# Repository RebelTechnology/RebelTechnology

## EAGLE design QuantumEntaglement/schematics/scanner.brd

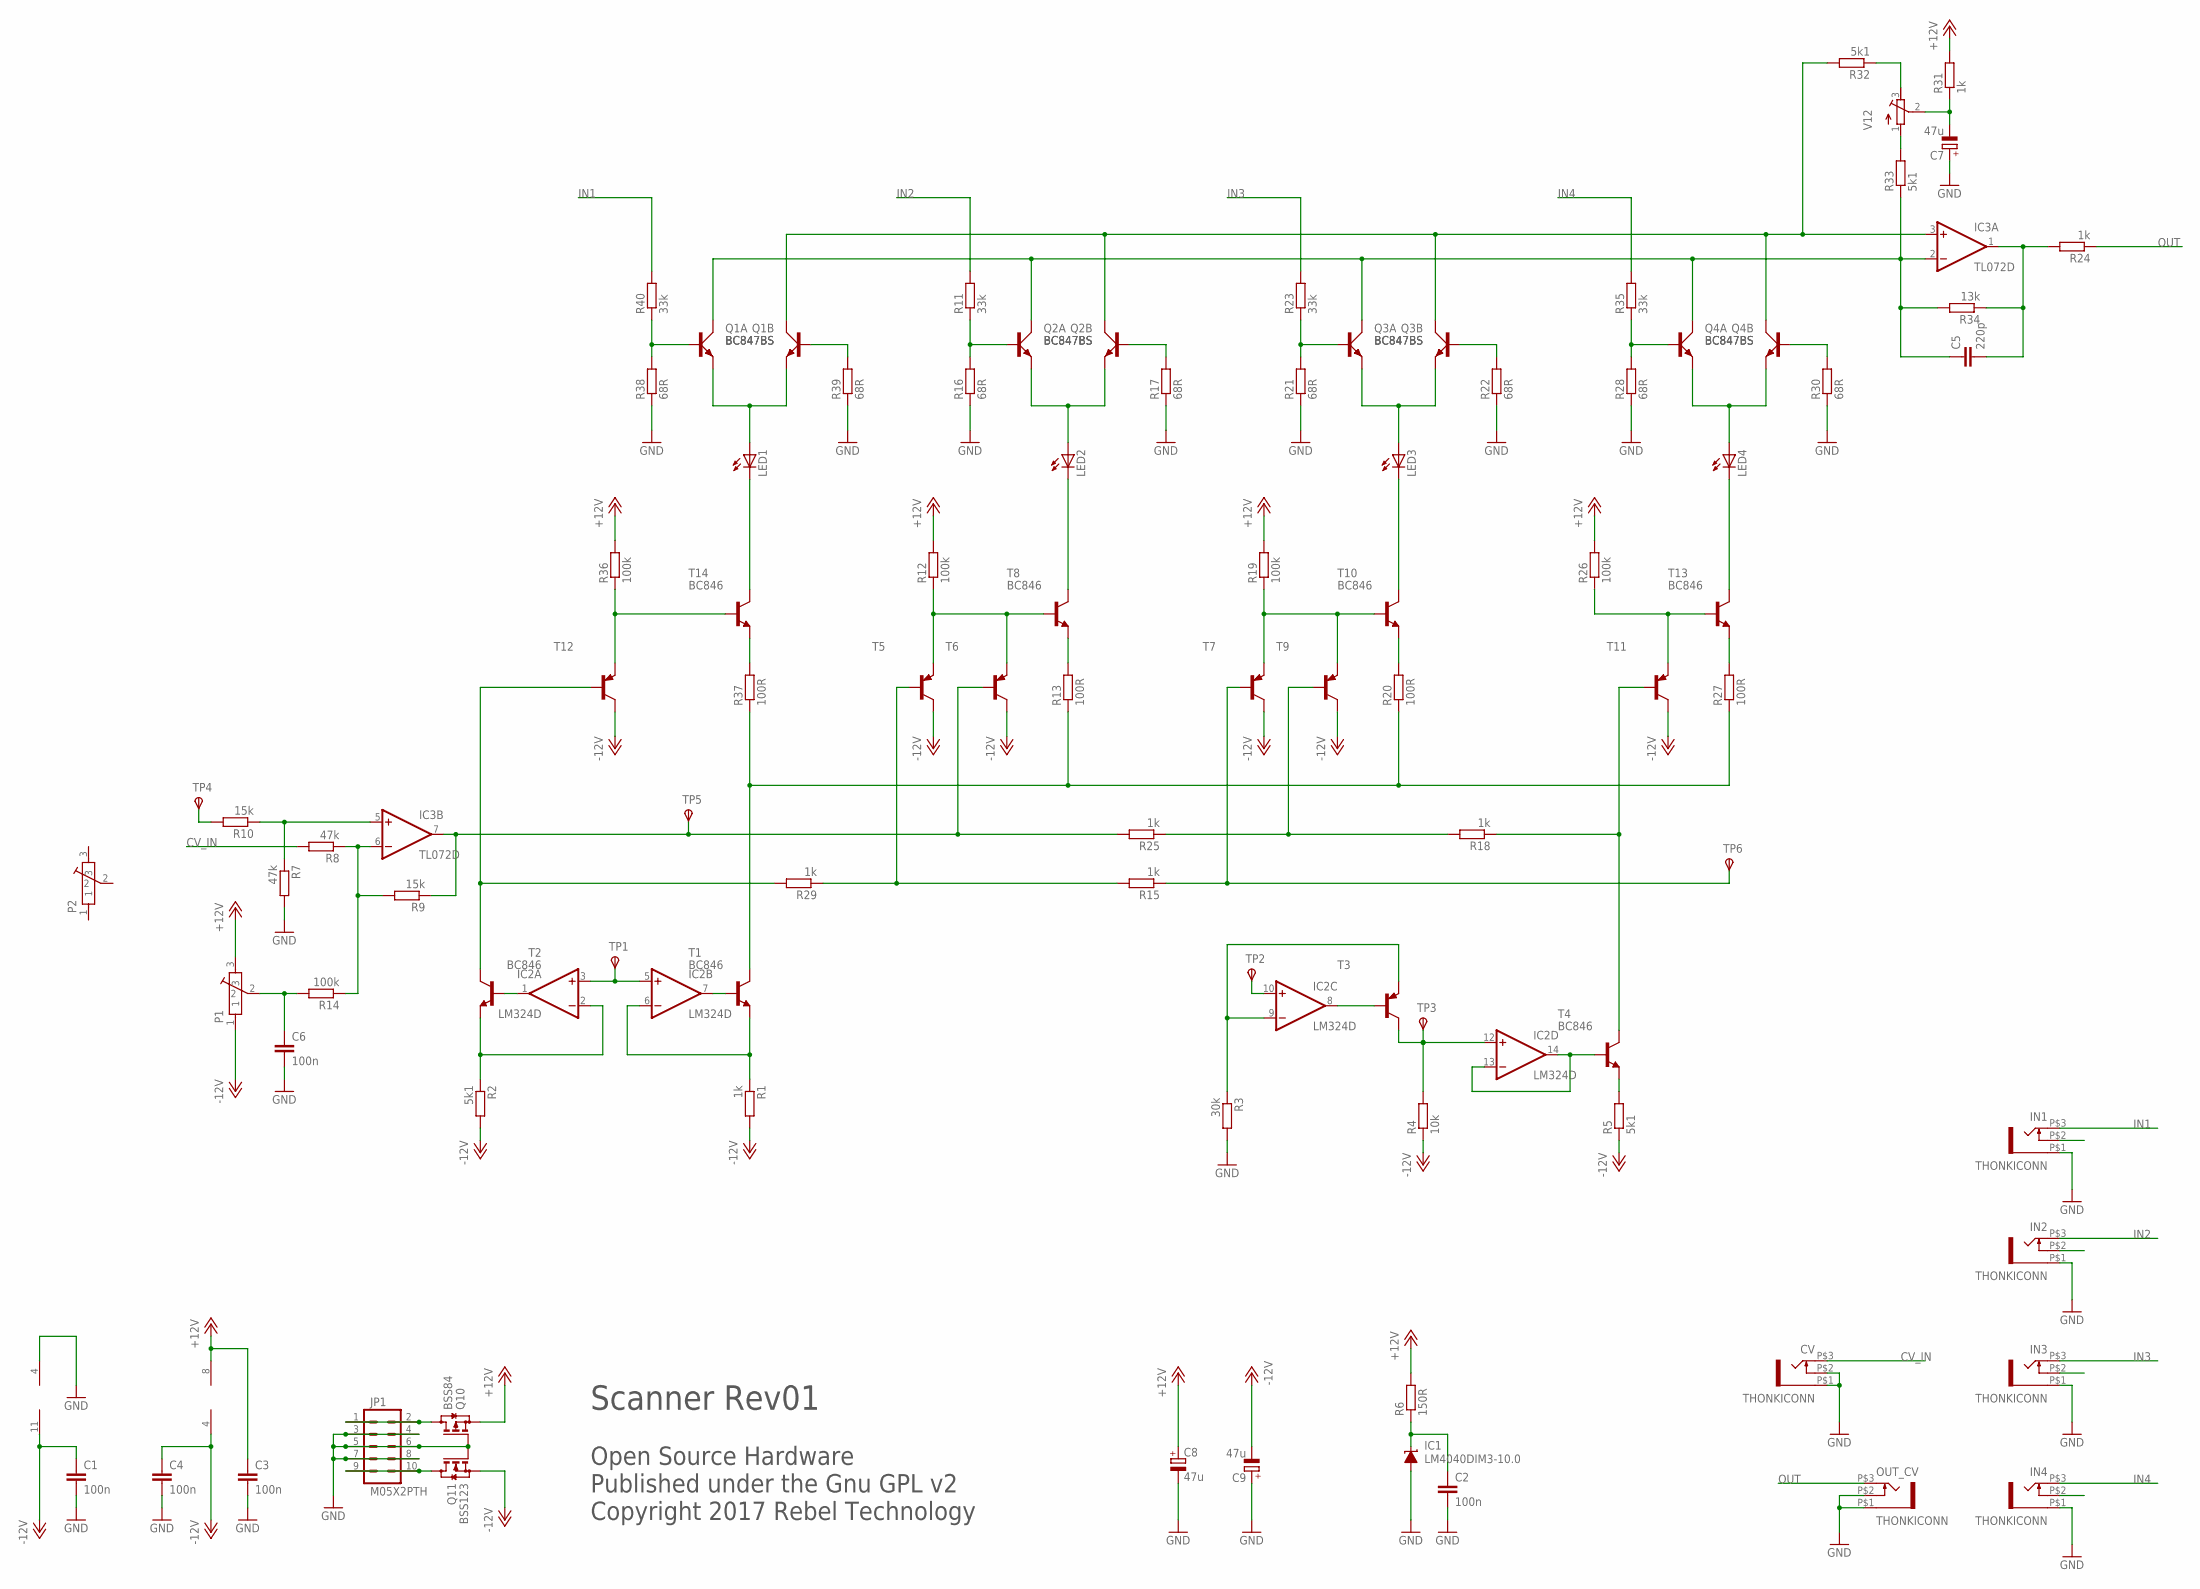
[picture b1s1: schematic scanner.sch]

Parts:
C1, C2, C3, C4, C6: 100n; C0603
C5: 220p; C0603
C7, C8, C9: 47u; CPOL-5
CV: THONKICONN
IC1: LM4040DIM3-10.0; DBZ_R-PDSO-G3
IC2: LM324D; SO14
IC3: TL072D; SO08
IN1, IN2, IN3, IN4: THONKICONN
JP1: M05X2PTH; AVR_ICSP
LED1, LED2, LED3, LED4: LED3MM
OUT_CV: THONKICONN
P1, P2: POT-ALPS-RK09L1140
Q1, Q2, Q3, Q4: BC847BS; SOT363_PHILIPS
Q10: BSS84; SOT23
Q11: BSS123; SOT23
R1, R15, R18, R24, R25, R29, R31: 1k; 0603
R2, R5, R32, R33: 5k1; 0603
R3: 30k; 0603
R4: 10k; 0603
R6: 150R; 0603
R7, R8: 47k; 0603
R9, R10: 15k; 0603
R11, R23, R35, R40: 33k; 0603
R12, R14, R19, R26, R36: 100k; 0603
R13, R20, R27, R37: 100R; 0603
R16, R17, R21, R22, R28, R30, R38, R39: 68R; 0603
R34: 13k; 0603
T1, T2, T4, T8, T10, T13, T14: BC846; SOT23
T3, T5, T6, T7, T9, T11, T12: BC856A-PNP-SOT23-BEC; SOT23-BEC
TP1, TP2, TP3, TP4, TP5, TP6: TPSPAD1-13; P1-13
V12: R-TRIMM64W; RTRIM64W

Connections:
+12V: C3.1, C8.+, IC3.8 (V+), P1.3, Q10.2 (S), R6.2, R12.2, R19.2, R26.2, R31.2, R36.2
-12V: C1.1, C4.1, C9.-, IC2.11 (V-), IC3.4 (V-), P1.1, Q11.2 (S), R1.2, R2.2, R4.1, R5.1, T5.C, T6.C, T7.C, T9.C, T11.C, T12.C
CV_IN: CV.P$3 (3), R8.2
GND: C1.2, C2.2, C3.2, C4.2, C6.2, C7.+, C8.-, C9.+, CV.P$1 (5), CV.P$2 (4), IC1.2 (A), IC2.4 (V+), IN1.P$1 (5), IN2.P$1 (5), IN3.P$1 (5), IN4.P$1 (5), JP1.3, JP1.4, JP1.5, JP1.6, JP1.7, JP1.8, OUT_CV.P$1 (5), OUT_CV.P$2 (4), Q10.1 (G), Q11.1 (G), R3.2, R7.2, R16.1, R17.1, R21.1, R22.1, R28.1, R30.1, R38.1, R39.1
IN1: IN1.P$3 (3), R40.2
IN2: IN2.P$3 (3), R11.2
IN3: IN3.P$3 (3), R23.2
IN4: IN4.P$3 (3), R35.2
unnamed: JP1.9, JP1.10, Q11.3 (D)
unnamed: C6.1, P1.2, R14.2
unnamed: Q3.2 (B), R21.2, R23.1
unnamed: Q3.5 (B), R22.2
unnamed: LED3.A, Q3.1 (E), Q3.4 (E)
unnamed: R19.1, T7.E, T9.E, T10.1 (B)
unnamed: LED3.K (C), T10.3 (C)
unnamed: R20.2, T10.2 (E)
unnamed: R18.1, T4.3 (C), T11.B
unnamed: R15.1, T7.B, TP6.TP
unnamed: C5.1, IC3.2 (-IN), Q1.6 (C), Q2.6 (C), Q3.6 (C), Q4.6 (C), R33.1, R34.2
unnamed: R18.2, R25.1, T9.B
unnamed: R13.1, R20.1, R27.1, R37.1, T1.3 (C)
unnamed: IC2.13 (-IN), IC2.14 (OUT), T4.1 (B)
unnamed: IC2.8 (OUT), T3.B
unnamed: IC2.12 (+IN), R4.2, T3.C, TP3.TP
unnamed: R5.2, T4.2 (E)
unnamed: IC2.9 (-IN), R3.1, T3.E
unnamed: IC2.10 (+IN), TP2.TP
unnamed: IC2.1 (OUT), T2.1 (B)
unnamed: IC2.7 (OUT), T1.1 (B)
unnamed: IC2.3 (+IN), IC2.5 (+IN), TP1.TP
unnamed: IC2.6 (-IN), R1.1, T1.2 (E)
unnamed: IC2.2 (-IN), R2.1, T2.2 (E)
unnamed: IC3.6 (-IN), R8.1, R9.2, R14.1
unnamed: R10.2, TP4.TP
unnamed: IC3.5 (+IN), R7.1, R10.1
unnamed: JP1.1, JP1.2, Q10.3 (D)
unnamed: C2.1, IC1.1 (C), R6.1
unnamed: C5.2, IC3.1 (OUT), R24.2, R34.1
unnamed: R33.2, V12.1 (A)
unnamed: R32.1, V12.3 (E)
unnamed: C7.-, R31.1, V12.2 (S)
unnamed: Q4.2 (B), R28.2, R35.1
unnamed: Q4.5 (B), R30.2
unnamed: LED4.A, Q4.1 (E), Q4.4 (E)
unnamed: R26.1, T11.E, T13.1 (B)
unnamed: LED4.K (C), T13.3 (C)
unnamed: R27.2, T13.2 (E)
unnamed: R29.2, T2.3 (C), T12.B
unnamed: IC3.7 (OUT), R9.1, R25.2, T6.B, TP5.TP
unnamed: Q2.2 (B), R11.1, R16.2
unnamed: Q2.5 (B), R17.2
unnamed: LED2.A, Q2.1 (E), Q2.4 (E)
unnamed: R12.1, T5.E, T6.E, T8.1 (B)
unnamed: LED2.K (C), T8.3 (C)
unnamed: R13.2, T8.2 (E)
unnamed: IC3.3 (+IN), Q1.3 (C), Q2.3 (C), Q3.3 (C), Q4.3 (C), R32.2
unnamed: Q1.2 (B), R38.2, R40.1
unnamed: Q1.5 (B), R39.2
unnamed: LED1.A, Q1.1 (E), Q1.4 (E)
unnamed: R36.1, T12.E, T14.1 (B)
unnamed: LED1.K (C), T14.3 (C)
unnamed: R37.2, T14.2 (E)
unnamed: R15.2, R29.1, T5.B
OUT: OUT_CV.P$3 (3), R24.1

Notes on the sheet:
Open Source Hardware Published under the Gnu GPL v2 Copyright 2017 Rebel Technology
Scanner Rev01

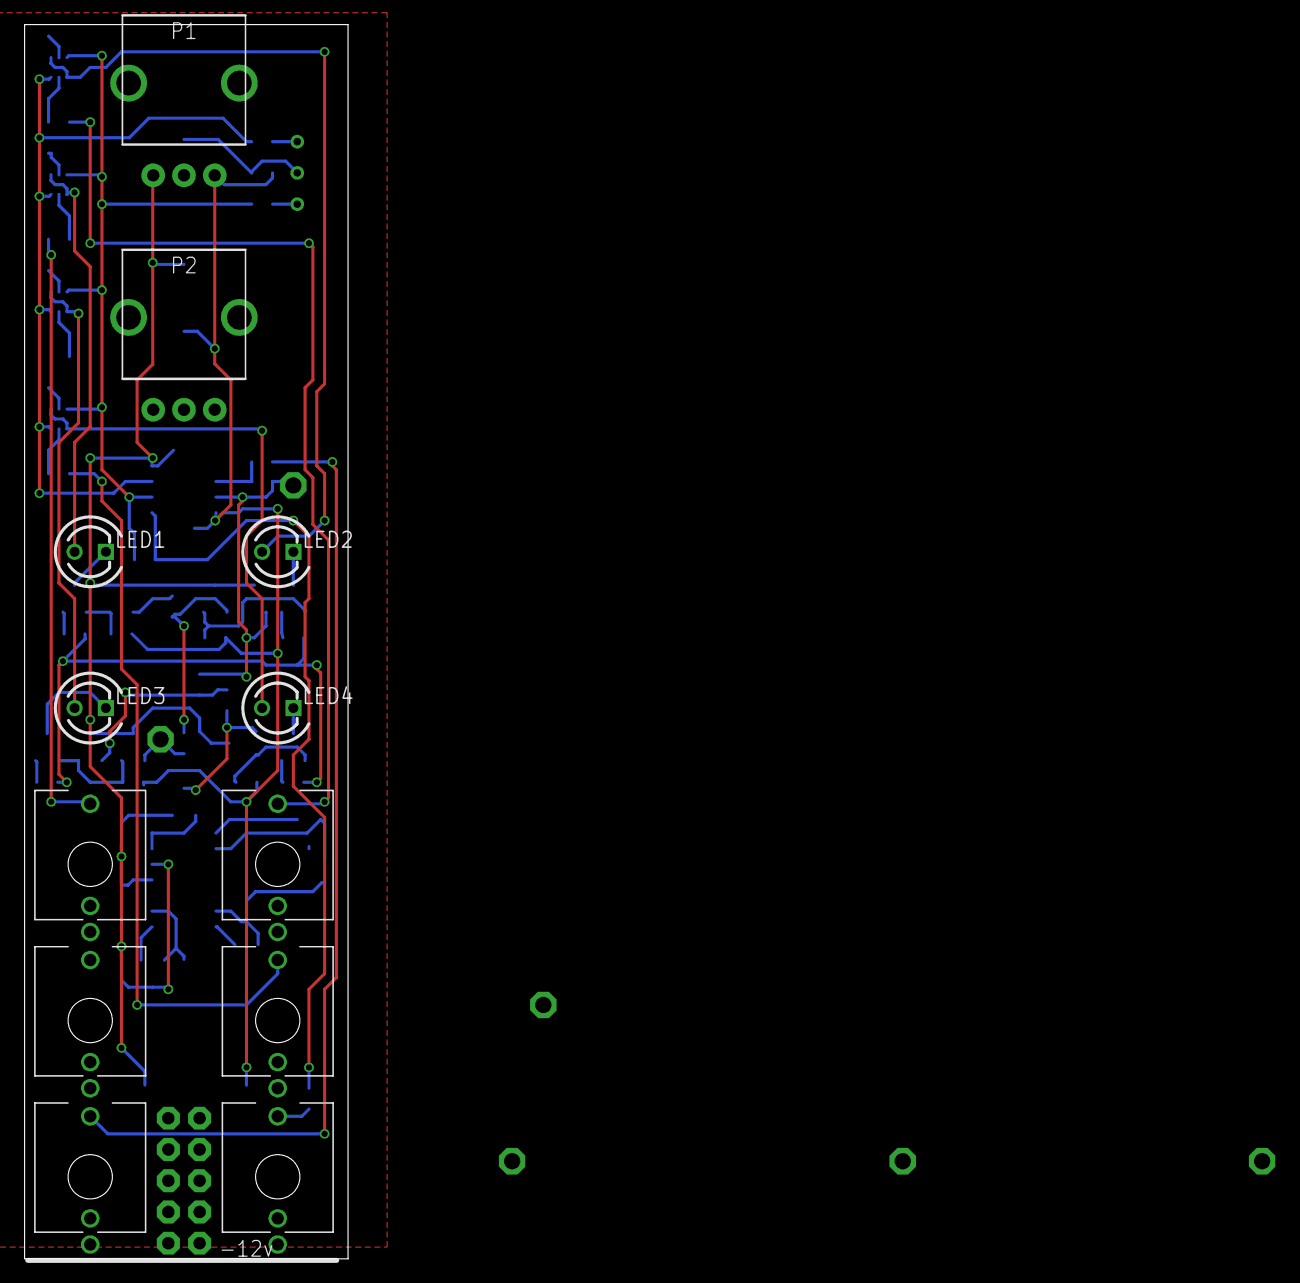
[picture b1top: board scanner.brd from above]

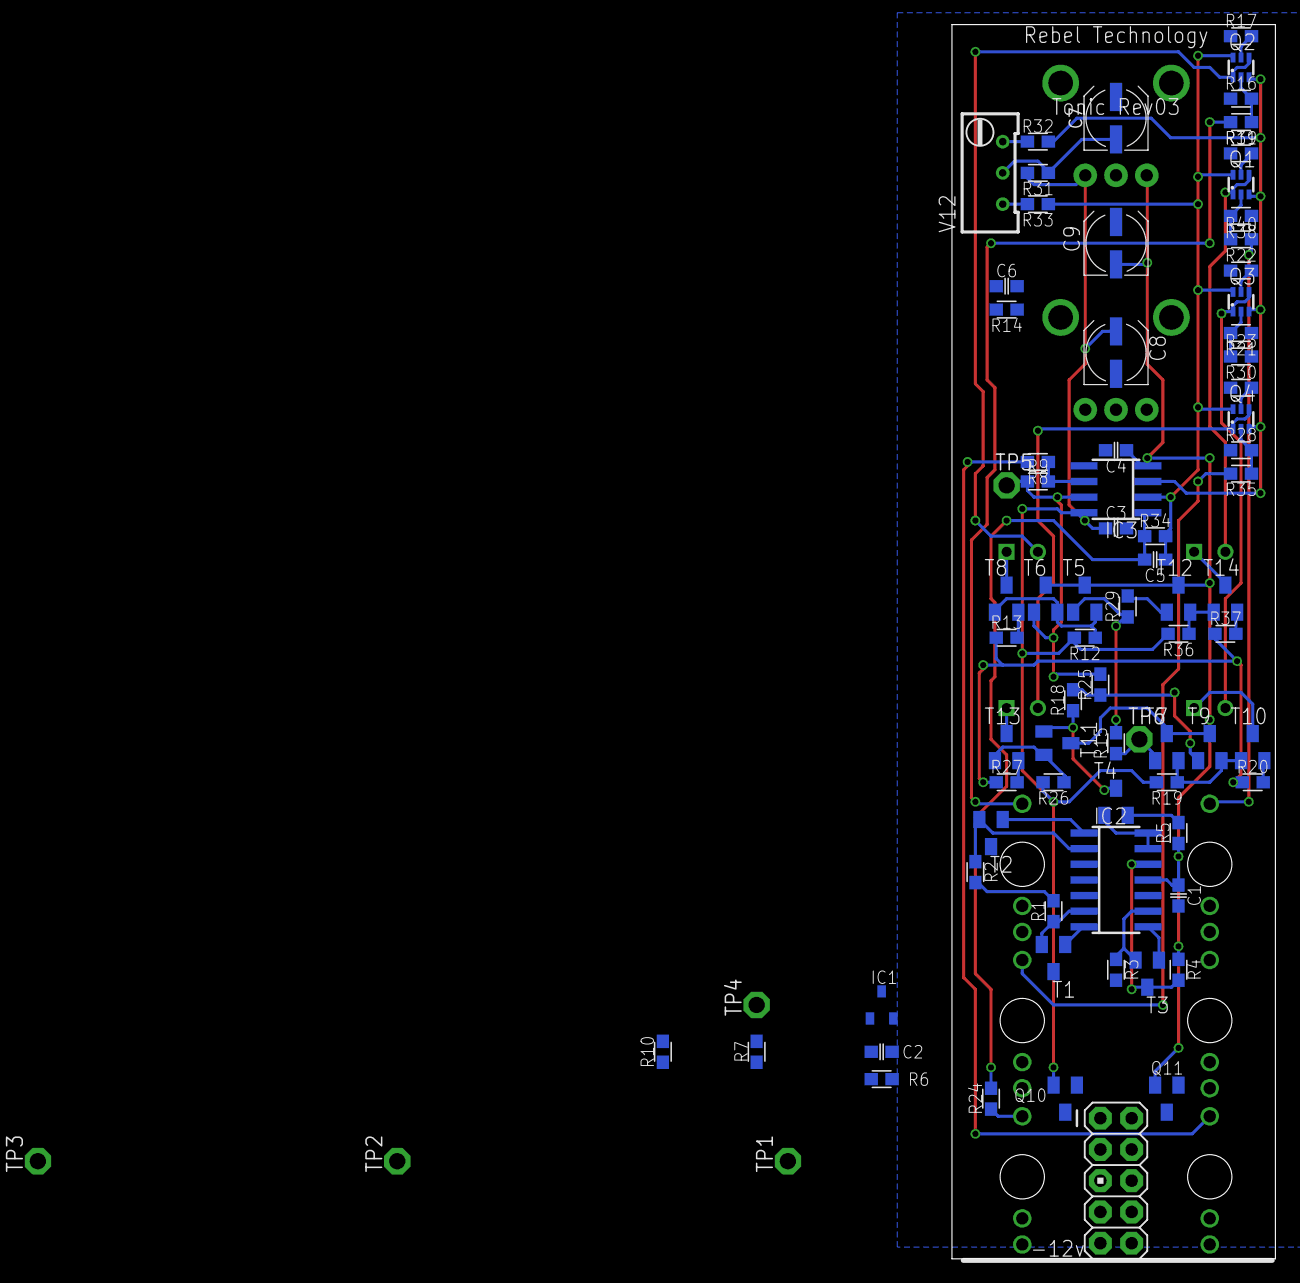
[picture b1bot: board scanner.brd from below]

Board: 2 copper layers, 26.3 x 100.3 mm, 92 parts (80 on the bottom side), 64 nets.

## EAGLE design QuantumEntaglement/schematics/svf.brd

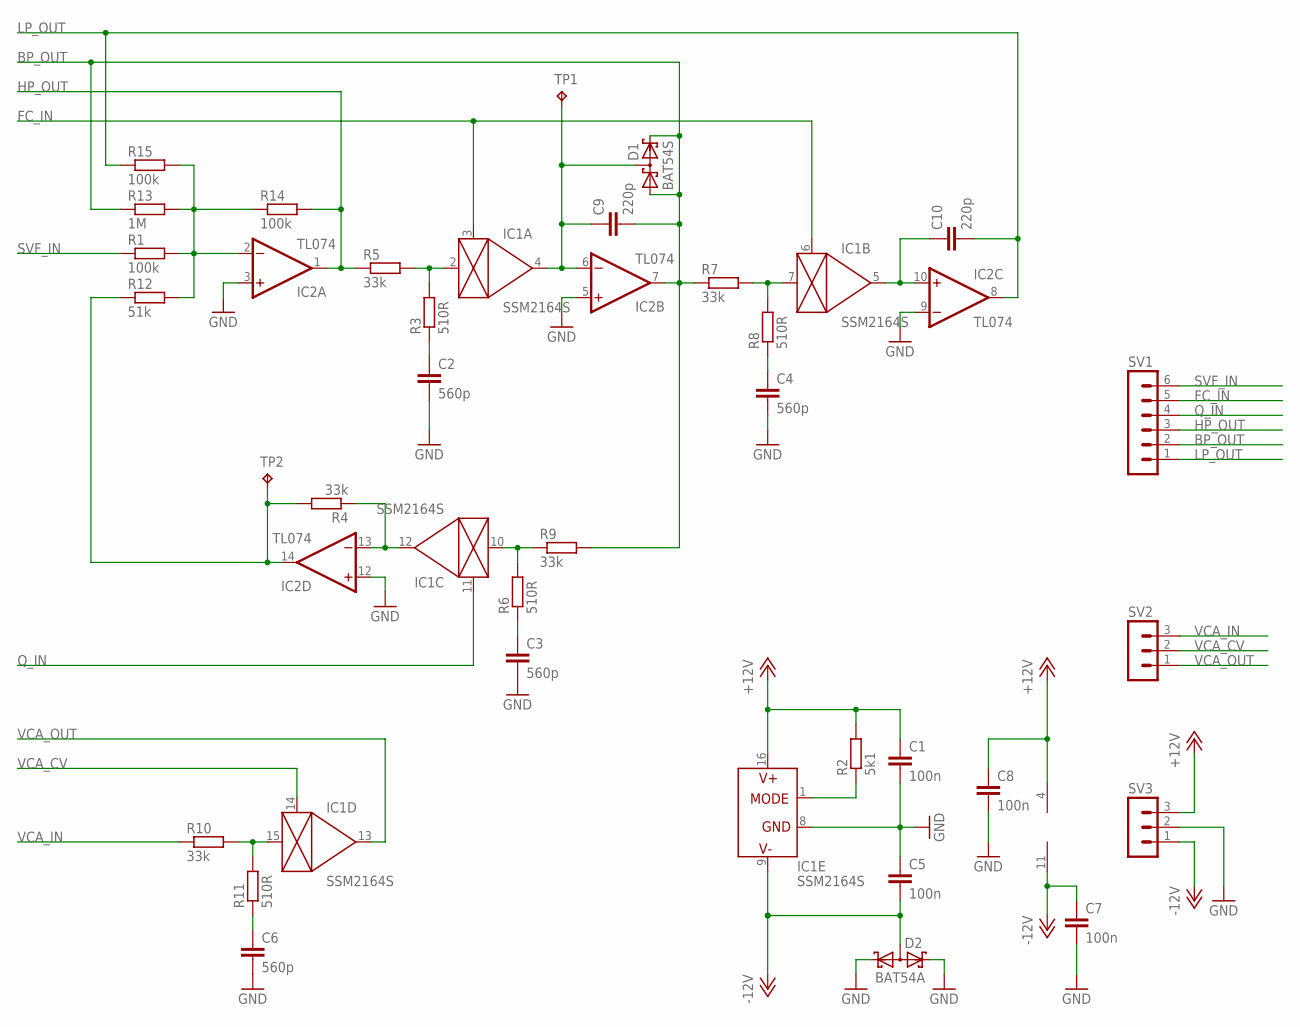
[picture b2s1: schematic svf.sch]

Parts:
C1, C5, C7, C8: 100n; C0603
C2, C3, C4, C6: 560p; C0603
C9, C10: 220p; C0603
D1: BAT54S; SOT23
D2: BAT54A; SOT23
IC1: SSM2164S; SOIC16N
IC2: TL074; SO14
R1, R14, R15: 100k; 0603
R2: 5k1; 0603
R3, R6, R8, R11: 510R; 0603
R4, R5, R7, R9, R10: 33k; 0603
R12: 51k; 0603
R13: 1M; 0603
SV1: MA06-1
SV2, SV3: MA03-1
TP1, TP2: TPPAD1-13; P1-13

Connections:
+12V: C1.1, C8.1, IC1.16 (V+), IC2.4 (V+), R2.2, SV3.3
-12V: C5.2, C7.1, D2.3 (AA), IC1.9 (V-), IC2.11 (V-), SV3.1
BP_OUT: C9.2, D1.1 (A1), D1.2 (C2), IC2.7 (OUT), R7.1, R9.2, R13.1, SV1.2
FB_IN: IC2.14 (OUT), R4.2, R12.1, TP2.TP
FC_IN: IC1.3 (CTRL), IC1.6 (CTRL), SV1.5
GND: C1.2, C2.2, C3.2, C4.2, C5.1, C6.2, C7.2, C8.2, D2.1 (K1), D2.2 (K2), IC1.8 (GND), IC2.3 (+IN), IC2.5 (+IN), IC2.9 (-IN), IC2.12 (+IN), SV3.2
HP_OUT: IC2.1 (OUT), R5.1, R14.2, SV1.3
LP_OUT: C10.2, IC2.8 (OUT), R15.1, SV1.1
unnamed: IC1.1 (MODE), R2.1
unnamed: IC1.7 (IN), R7.2, R8.2
unnamed: C4.1, R8.1
unnamed: C10.1, IC1.5 (OUT), IC2.10 (+IN)
unnamed: IC1.12 (OUT), IC2.13 (-IN), R4.1
unnamed: IC2.2 (-IN), R1.2, R12.2, R13.2, R14.1, R15.2
unnamed: C6.1, R11.1
unnamed: C9.1, D1.3 (C1A2), IC1.4 (OUT), IC2.6 (-IN), TP1.TP
unnamed: IC1.10 (IN), R6.2, R9.1
unnamed: IC1.15 (IN), R10.2, R11.2
unnamed: C3.1, R6.1
unnamed: IC1.2 (IN), R3.2, R5.2
unnamed: C2.1, R3.1
Q_IN: IC1.11 (CTRL), SV1.4
SVF_IN: R1.1, SV1.6
VCA_CV: IC1.14 (CTRL), SV2.2
VCA_IN: R10.1, SV2.3
VCA_OUT: IC1.13 (OUT), SV2.1

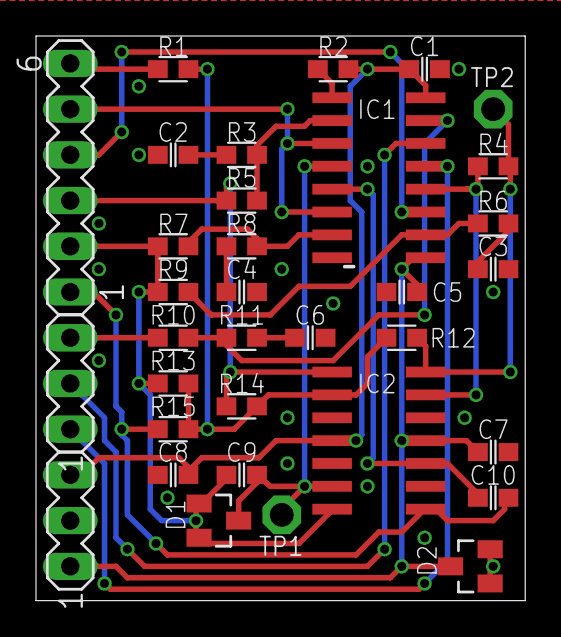
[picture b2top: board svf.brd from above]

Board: 2 copper layers, 27.2 x 31.4 mm, 34 parts (0 on the bottom side), 26 nets.

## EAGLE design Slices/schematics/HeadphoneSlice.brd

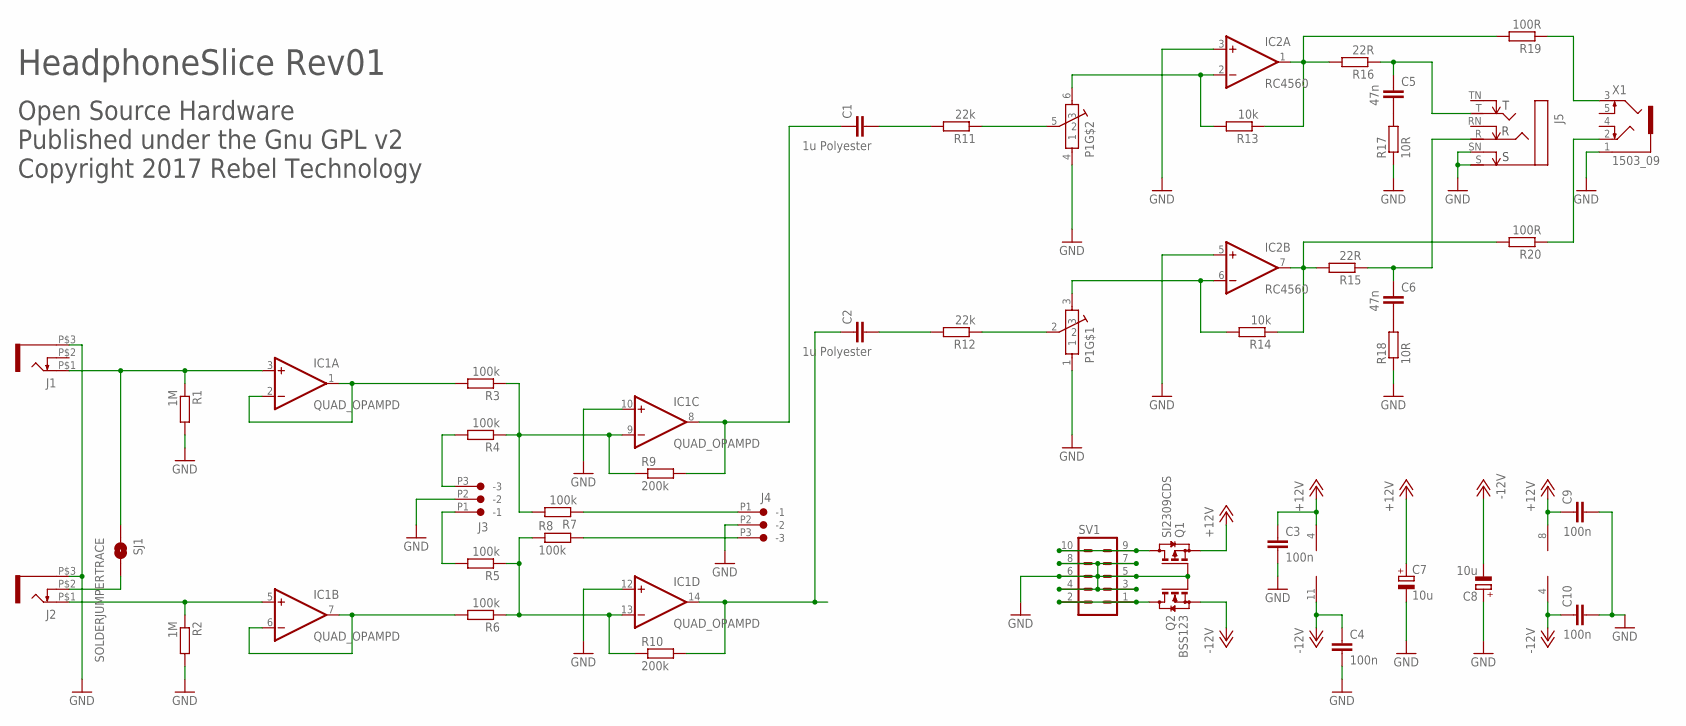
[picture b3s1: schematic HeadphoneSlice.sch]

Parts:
C1, C2: 1u Polyester; C1210
C3, C4, C9, C10: 100n; C0603
C5, C6: 47n; C0603
C7, C8: 10u; 153CLV-0505
IC1: QUAD_OPAMPD; SO14
IC2: RC4560; SO08
J1, J2: JACK-UJ-3502-RSLOT; UJ-3502-R-SLOT
J3, J4: CON-JST_PH_3W
J5: NEUTRIK_NRJ6HFSTD; NRJ6HF
P1: POT-BOURNS-PTD902
Q1: SI2309CDS; SOT23
Q2: BSS123; SOT23
R1, R2: 1M; 0603
R3, R4, R5, R6, R7, R8: 100k; 0603
R9, R10: 200k; 0603
R11, R12: 22k; 0603
R13, R14: 10k; 0603
R15, R16: 22R; 0603
R17, R18: 10R; 0603
R19, R20: 100R; 0603
SJ1: SOLDERJUMPERTRACE; SJ_2S-TRACE
SV1: MA05-2
X1: 1503_09

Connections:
+12V: C3.1, C7.+, C9.1, IC1.4 (V+), IC2.8 (V+), Q1.2 (S)
-12V: C4.1, C8.-, C10.1, IC1.11 (V-), IC2.4 (V-), Q2.2 (S)
BUS_IN_L: J3.P3 (-3), R4.2
BUS_IN_R: J3.P1 (-1), R5.2
GND: C3.2, C4.2, C7.-, C8.+, C9.2, C10.2, IC1.10 (+IN), IC1.12 (+IN), IC2.3 (+IN), IC2.5 (+IN), J1.P$3 (SLEEVE), J2.P$3 (SLEEVE), J3.P2 (-2), J4.P2 (-2), J5.S, J5.SN, P1.1, P1.4 (1), Q1.1 (G), Q2.1 (G), R1.2, R2.2, R17.1, R18.1, SV1.3, SV1.4, SV1.5, SV1.6, SV1.7, SV1.8, X1.1
HP_L: C5.1, J5.T, R16.1
HP_R: C6.1, J5.R, R15.1
IN_B1: J2.P$2 (SW), SJ1.2
IN_L: IC1.3 (+IN), J1.P$1 (TIP), R1.1, SJ1.1
IN_R: IC1.5 (+IN), J2.P$1 (TIP), R2.1
LINE_L: R19.1, X1.3
LINE_R: R20.1, X1.2
unnamed: Q2.3 (D), SV1.1, SV1.2
unnamed: IC2.7 (OUT), R14.1, R15.2, R20.2
unnamed: IC2.2 (-IN), P1.6 (3), R13.2
unnamed: C2.2, R12.2
unnamed: P1.5 (2), R11.1
unnamed: P1.2, R12.1
unnamed: C2.1, IC1.14 (OUT), R10.2
unnamed: C1.2, R11.2
unnamed: C1.1, IC1.8 (OUT), R9.2
unnamed: IC1.6 (-IN), IC1.7 (OUT), R6.2
unnamed: C6.2, R18.2
unnamed: IC1.1 (OUT), IC1.2 (-IN), R3.2
unnamed: Q1.3 (D), SV1.9, SV1.10
unnamed: IC2.6 (-IN), P1.3, R14.2
unnamed: IC2.1 (OUT), R13.1, R16.2, R19.2
unnamed: J4.P1 (-1), R7.1
unnamed: C5.2, R17.2
unnamed: J4.P3 (-3), R8.2
unnamed: IC1.13 (-IN), R5.1, R6.1, R8.1, R10.1
unnamed: IC1.9 (-IN), R3.1, R4.1, R7.2, R9.1

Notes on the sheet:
Open Source Hardware Published under the Gnu GPL v2 Copyright 2017 Rebel Technology
HeadphoneSlice Rev01

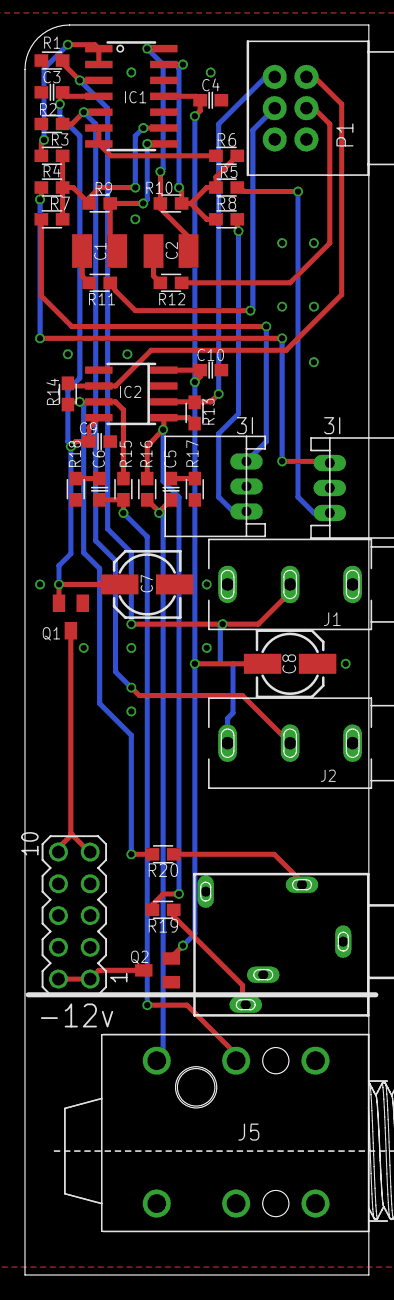
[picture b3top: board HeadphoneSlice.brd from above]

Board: 2 copper layers, 27.5 x 100.0 mm, 43 parts (1 on the bottom side), 32 nets.

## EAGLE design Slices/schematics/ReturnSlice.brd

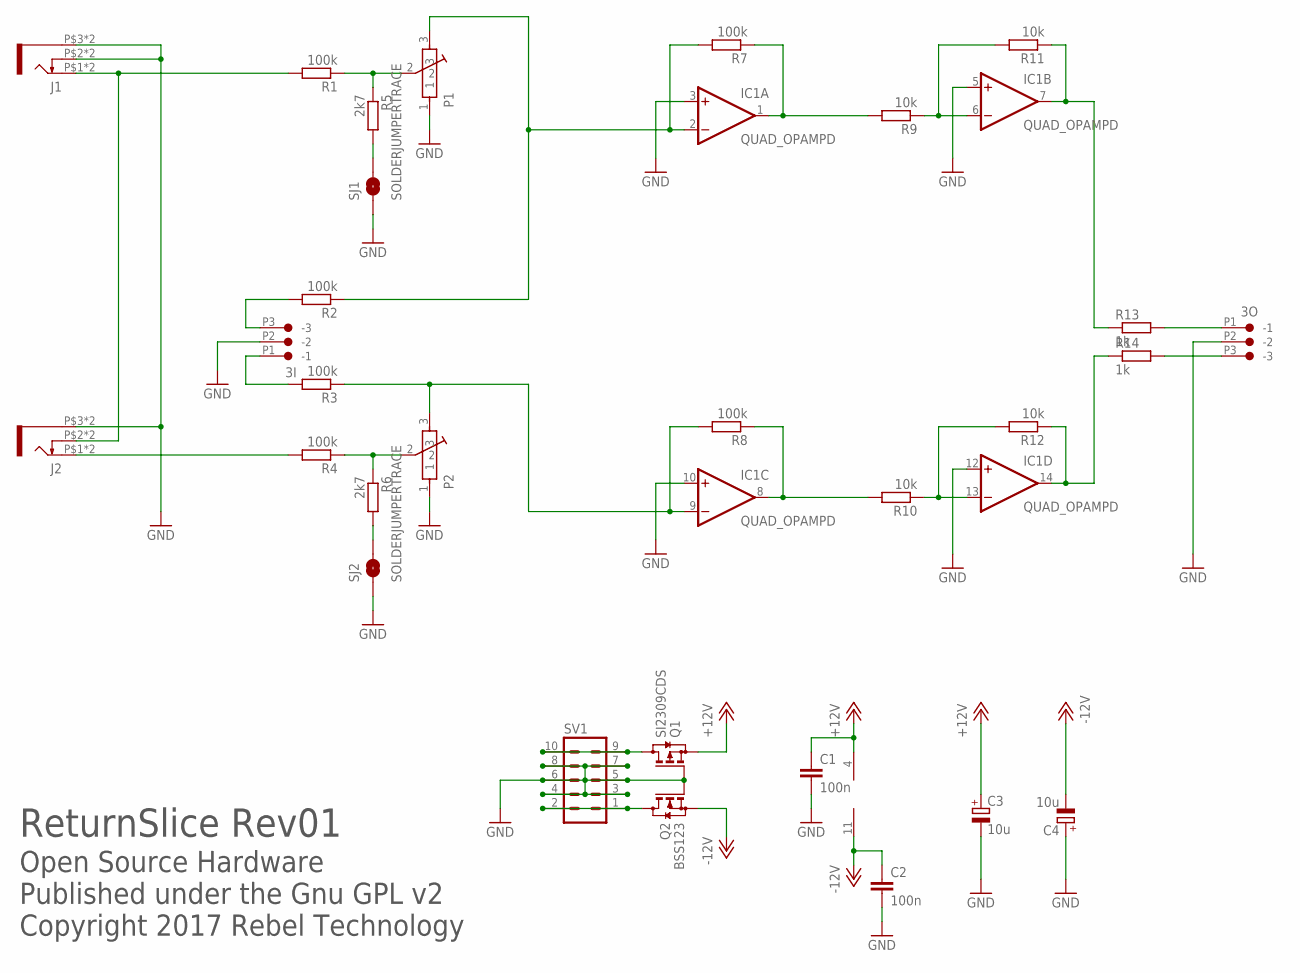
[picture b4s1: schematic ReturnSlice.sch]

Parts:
3I, 3O: CON-JST_PH_3W
C1, C2: 100n; C0603
C3, C4: 10u; 153CLV-0505
IC1: QUAD_OPAMPD; SO14
J1, J2: JACK-UJ-3502-RSLOT; UJ-3502-R-SLOT
P1, P2: 10k; POT-BOURNS-PTD901
Q1: SI2309CDS; SOT23
Q2: BSS123; SOT23
R1, R2, R3, R4, R7, R8: 100k; 0603
R5, R6: 2k7; 0603
R9, R10, R11, R12: 10k; 0603
R13, R14: 1k; 0603
SJ1, SJ2: SOLDERJUMPERTRACE; SJ_2S-TRACE
SV1: MA05-2

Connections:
+12V: C1.1, C3.+, IC1.4 (V+), Q1.2 (S)
-12V: C2.1, C4.-, IC1.11 (V-), Q2.2 (S)
GND: 3I.P2 (-2), 3O.P2 (-2), C1.2, C2.2, C3.-, C4.+, IC1.3 (+IN), IC1.5 (+IN), IC1.10 (+IN), IC1.12 (+IN), J1.P$2 (SW), J1.P$2B (SW), J1.P$3 (SLEEVE), J1.P$3B (SLEEVE), J2.P$3 (SLEEVE), J2.P$3B (SLEEVE), P1.1, P2.1, Q1.1 (G), Q2.1 (G), SJ1.1, SJ2.1, SV1.3, SV1.4, SV1.5, SV1.6, SV1.7, SV1.8
IN_A: 3I.P3 (-3), R2.2
IN_L: J1.P$1 (TIP), J1.P$1B (TIP), J2.P$2 (SW), J2.P$2B (SW), R1.2
IN_R: J2.P$1 (TIP), J2.P$1B (TIP), R4.2
unnamed: Q2.3 (D), SV1.1, SV1.2
unnamed: R5.2, SJ1.2
unnamed: R6.2, SJ2.2
unnamed: IC1.9 (-IN), P2.3, R3.1, R8.2
unnamed: IC1.6 (-IN), R9.1, R11.2
unnamed: 3O.P1 (-1), R13.2
unnamed: 3O.P3 (-3), R14.2
unnamed: IC1.7 (OUT), R11.1, R13.1
unnamed: P2.2, R4.1, R6.1
unnamed: P1.2, R1.1, R5.1
unnamed: Q1.3 (D), SV1.9, SV1.10
unnamed: 3I.P1 (-1), R3.2
unnamed: IC1.2 (-IN), P1.3, R2.1, R7.2
unnamed: IC1.13 (-IN), R10.1, R12.2
unnamed: IC1.14 (OUT), R12.1, R14.1
unnamed: IC1.8 (OUT), R8.1, R10.2
unnamed: IC1.1 (OUT), R7.1, R9.2

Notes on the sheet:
Open Source Hardware Published under the Gnu GPL v2 Copyright 2017 Rebel Technology
ReturnSlice Rev01

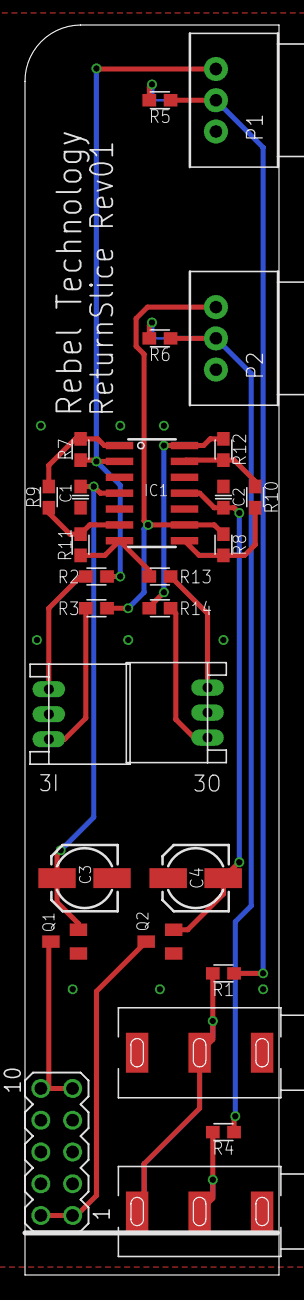
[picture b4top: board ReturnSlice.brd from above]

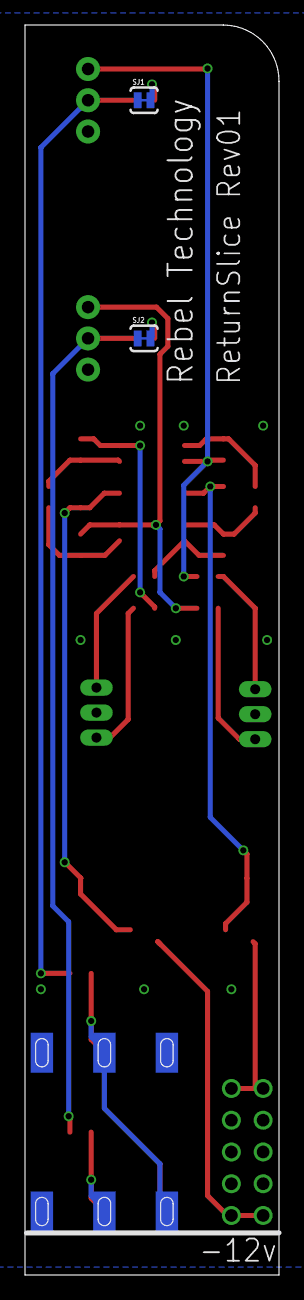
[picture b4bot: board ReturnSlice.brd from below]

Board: 2 copper layers, 20.3 x 100.0 mm, 30 parts (2 on the bottom side), 23 nets.

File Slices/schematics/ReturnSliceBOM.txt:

Partlist exported from C:/cygwin64/home/padski/RebelTechnology/Slices/schematics/ReturnSlice.sch at 17/01/2017 15:00

Qty Value              Device             Package           Parts                  Description                          
1                      MA05-2             MA05-2            SV1                    PIN HEADER                           
6   100k               R-EU_0603          0603              R1, R2, R3, R4, R7, R8 RESISTOR, European symbol            
2   100n               C-EUC0603          C0603             C1, C2                 CAPACITOR, European symbol           
2   10k                POT-BOURNS-PTD901  POT-BOURNS-PTD901 P1, P2                                                      
4   10k                R-EU_0603          0603              R9, R10, R11, R12      RESISTOR, European symbol            
2   10u                CPOL-EU153CLV-0505 153CLV-0505       C3, C4                 POLARIZED CAPACITOR, European symbol 
2   1k                 R-EU_0603          0603              R13, R14               RESISTOR, European symbol            
2   2k7                R-EU_0603          0603              R5, R6                 RESISTOR, European symbol            
1   BSS123             BSS123             SOT23             Q2                     N-CHANNEL MOS FET                    
2   CON-JST_PH_3W      CON-JST_PH_3W      CON-JST_PH_3W     3I, 3O                                                      
2   JACK-UJ-3502-RSLOT JACK-UJ-3502-RSLOT UJ-3502-R-SLOT    J1, J2                                                      
1   QUAD_OPAMPD        QUAD_OPAMPD        SO14              IC1                    OP AMP                               
1   SI2309CDS          BSS84              SOT23             Q1                     P-CHANNEL MOS FET                    
2   SOLDERJUMPERTRACE  SOLDERJUMPERTRACE  SJ_2S-TRACE       SJ1, SJ2               Solder Jumper

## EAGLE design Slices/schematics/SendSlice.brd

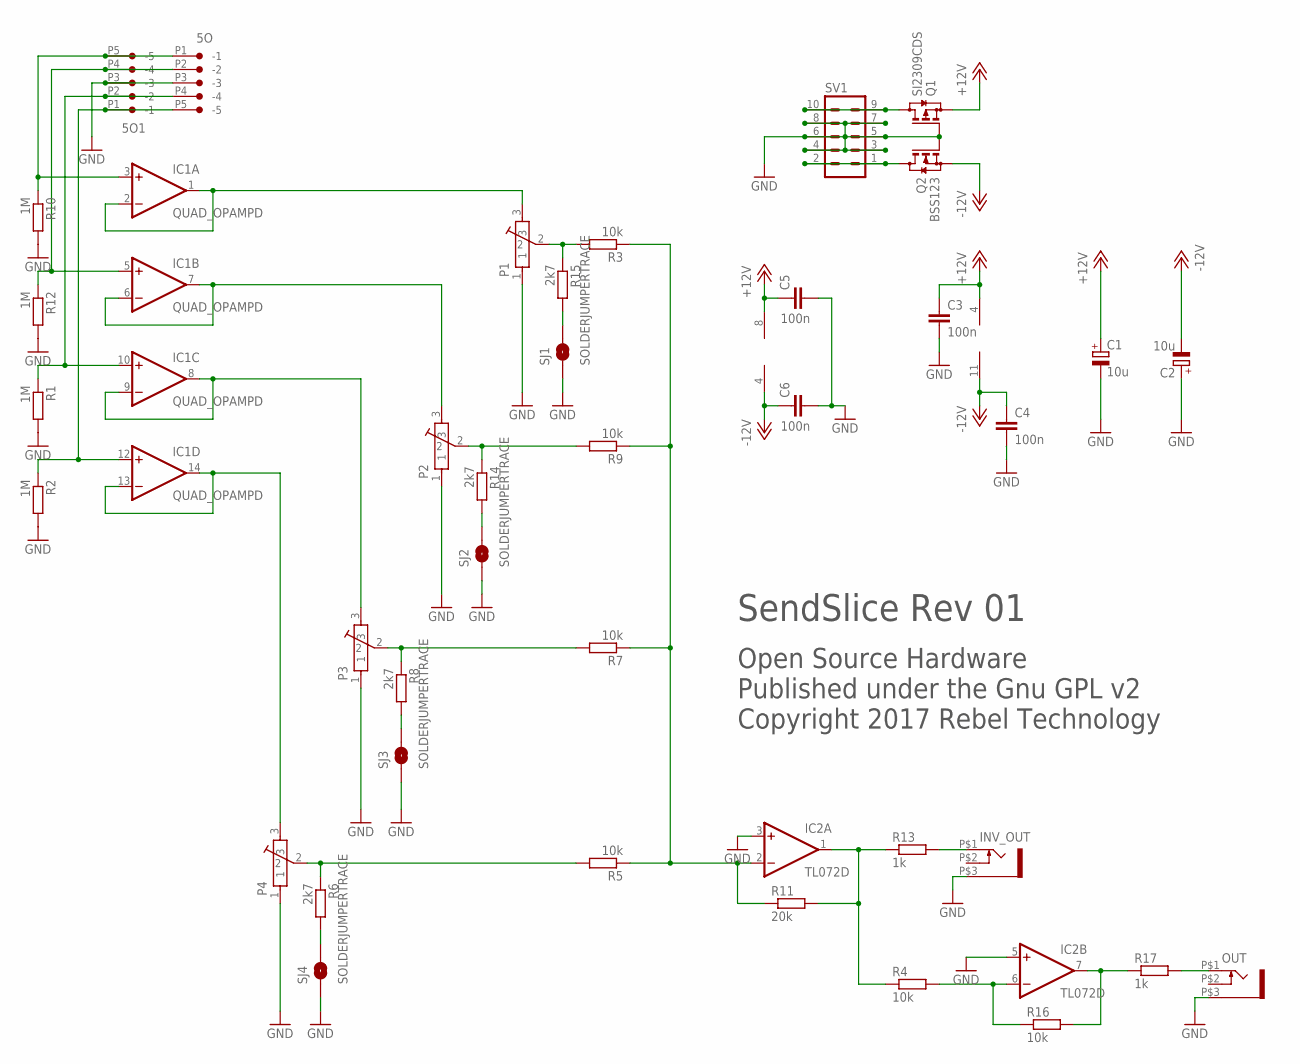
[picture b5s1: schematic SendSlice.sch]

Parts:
5O, 5O1: CON-JST_PH_5W
C1, C2: 10u; 153CLV-0505
C3, C4, C5, C6: 100n; C0603
IC1: QUAD_OPAMPD; SO14
IC2: TL072D; SO08
INV_OUT: JACK-UJ-3502-R; UJ-3502-R
OUT: JACK-UJ-3502-R; UJ-3502-R
P1, P2, P3, P4: 10k lin; POT-BOURNS-PTD901
Q1: SI2309CDS; SOT23
Q2: BSS123; SOT23
R1, R2, R10, R12: 1M; 0603
R3, R4, R5, R7, R9, R16: 10k; 0603
R6, R8, R14, R15: 2k7; 0603
R11: 20k; 0603
R13, R17: 1k; 0603
SJ1, SJ2, SJ3, SJ4: SOLDERJUMPERTRACE; SJ_2S-TRACE
SV1: MA05-2

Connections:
+12V: C1.+, C3.1, C5.1, IC1.4 (V+), IC2.8 (V+), Q1.2 (S)
-12V: C2.-, C4.1, C6.1, IC1.11 (V-), IC2.4 (V-), Q2.2 (S)
GND: 5O.P3 (-3), 5O1.P3 (-3), C1.-, C2.+, C3.2, C4.2, C5.2, C6.2, IC2.3 (+IN), IC2.5 (+IN), INV_OUT.P$3 (SLEEVE), OUT.P$3 (SLEEVE), P1.1, P2.1, P3.1, P4.1, Q1.1 (G), Q2.1 (G), R1.2, R2.2, R10.2, R12.2, SJ1.1, SJ2.1, SJ3.1, SJ4.1, SV1.3, SV1.4, SV1.5, SV1.6, SV1.7, SV1.8
IN_1: 5O.P1 (-1), 5O1.P5 (-5), IC1.3 (+IN), R10.1
IN_2: 5O.P2 (-2), 5O1.P4 (-4), IC1.5 (+IN), R12.1
IN_3: 5O.P4 (-4), 5O1.P2 (-2), IC1.10 (+IN), R1.1
IN_4: 5O.P5 (-5), 5O1.P1 (-1), IC1.12 (+IN), R2.1
unnamed: Q2.3 (D), SV1.1, SV1.2
unnamed: P2.2, R9.2, R14.1
unnamed: P1.2, R3.2, R15.1
unnamed: IC1.6 (-IN), IC1.7 (OUT), P2.3
unnamed: IC1.1 (OUT), IC1.2 (-IN), P1.3
unnamed: IC2.1 (OUT), R4.1, R11.2, R13.1
unnamed: IC2.7 (OUT), R16.2, R17.1
unnamed: IC2.2 (-IN), R3.1, R5.1, R7.1, R9.1, R11.1
unnamed: INV_OUT.P$1 (TIP), R13.2
unnamed: R15.2, SJ1.2
unnamed: IC1.13 (-IN), IC1.14 (OUT), P4.3
unnamed: R6.2, SJ4.2
unnamed: IC1.8 (OUT), IC1.9 (-IN), P3.3
unnamed: Q1.3 (D), SV1.9, SV1.10
unnamed: R8.2, SJ3.2
unnamed: R14.2, SJ2.2
unnamed: IC2.6 (-IN), R4.2, R16.1
unnamed: OUT.P$1 (TIP), R17.2
unnamed: P4.2, R5.2, R6.1
unnamed: P3.2, R7.2, R8.1

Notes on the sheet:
Open Source Hardware Published under the Gnu GPL v2 Copyright 2017 Rebel Technology
SendSlice Rev 01

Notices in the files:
parts and their libraries:
SparkFun: Licensing: CC v3.0 Share-Alike You are welcome to use this library for commercial purposes.
